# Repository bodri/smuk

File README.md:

# 🚀 smuk
An SMU by kapuki

This repository is structured as a unified monorepo containing both the physical hardware designs (schematics, PCB, enclosures) and the bare-metal C firmware.

---

## 📂 Project Architecture

The workspace is split into isolated modules to decouple hardware revisions from compilation build systems:

```text
smuk/
├── firmware/       # Core firmware application, drivers, and build targets
├── hardware/       # Electrical schematics, PCB layout, and production packages
├── AGENTS.md       # Target rules and context for AI assistants (Claude, Codex)
└── README.md       # This file
```

---

## 📐 1. Hardware Module (`/hardware`)

The electronics are designed using **KiCad 10.0** (or your preferred EDA tool), leveraging the high-performance capabilities of the **STM32H5** series (Cortex-M33 with TrustZone support).

### Key Subdirectories
* **`/pcb`**: Contains the source `.kicad_pro`, `.kicad_sch`, and `.kicad_pcb` files.
* **`/mechanical`**: STEP files for the enclosure, 3D component models, and mounting layouts.
* **`/production`**: **Production-ready files.** Check this folder if you need to quickly inspect the schematics without installing the full EDA design suite.

### Quick Hardware Access
* 📄 **Latest Schematic PDF**: [`/hardware/production/schematic.pdf`](hardware/production/) *(Update path to exact filename)*
* 📦 **Gerber Packages / BOM**: Prepared inside [`/hardware/production/`](hardware/production/) for direct manufacturing ordering.

---

## 💻 2. Firmware Module (`/firmware`)

The software environment is built on top of the **STM32 Cube Hardware Abstraction Layer (HAL)** and configured for cross-compilation using the **GNU ARM Embedded Toolchain**.

### Current Firmware Status

Firmware targets the **STM32H503RB**. ADS131M03 SPI/DMA acquisition, physical measurement conversion, CALBUS and voltage calibration, and persistent Flash calibration storage are working.

Range control, PA safety, watchdog, and parts of the platform interface still contain placeholders awaiting hardware integration. The `App` directory is unfinished and is excluded from the firmware source list.

### Core Architecture

```text
firmware/
├── Core/                 # CubeMX initialization, callbacks, integration loop
├── Drivers/SMU/          # ADC, measurement, calibration and hardware interfaces
├── Platform/STM32H503/   # Board-specific HAL implementations
├── Storage/             # Persistent calibration records and Flash storage
├── App/                 # Unfinished instrument/control implementation
├── tests/               # Host regression tests
└── smuk.ioc              # STM32CubeMX configuration
```

`Drivers` also contains the vendor CMSIS, STM32H5 HAL, and board support libraries. `Drivers/SMU/ads131m03.h/.c` contains both blocking device bring-up and DMA acquisition. Its HAL operations are provided through `ads131m03_port.h`, implemented in `Platform/STM32H503/ads131m03_port_hal.c`.

`smu_measurement` converts raw ADC samples into physical measurements and applies calibration and filtering. `smu_calibration` manages active coefficients, `smu_cal_seq` sequences calibration acquisition, and `Storage/calibration_store` persists calibration records.

> ⚠️ **Crucial Development Rule:** In CubeMX-generated files, write custom C code only inside the explicit `/* USER CODE BEGIN ... */` and `/* USER CODE END ... */` sections. Changes outside these sections may be lost when `smuk.ioc` is regenerated. This restriction does not apply to handwritten drivers and modules.

### Calibration Behavior

Calibration discard and acquisition phases each have a configurable timeout, defaulting to **1,000 ms** per phase. The sequencer accounts for elapsed scheduler time, including delayed ticks. On timeout, it opens calibration relays, selects zero CALBUS, requests PA disable and ranges off through the existing hardware interfaces, and latches a fault until sequencer reinitialization. PA and range actions still depend on the placeholder implementations described above.

Applying calibration coefficients preserves measurement ranges, validity/compliance/transition flags, sample count, and filter configuration. Filter history resets to avoid blending values from different calibrations, and cached outputs remain invalid until another frame is processed. Startup still performs full measurement initialization.

### Calibration Flash Reservation

Application Flash is limited to **112 KiB**, enforced by `check_limits.py` during the build. Two **8 KiB** calibration slots occupy the remaining 16 KiB:

| Region | Address range |
| --- | --- |
| Application | `0x08000000`–`0x0801BFFF` |
| Calibration A | `0x0801C000`–`0x0801DFFF` |
| Calibration B | `0x0801E000`–`0x0801FFFF` |

Saves replace the older or invalid slot and verify the replacement by record validation and byte-for-byte readback. The newest valid calibration is preserved while the replacement is written. Storage initialization does not erase calibration; loading falls back to default coefficients if neither slot is valid.

---

## 🛠️ Getting Started (Compilation & Flashing)

For project guidance, see [AGENTS.md](./AGENTS.md) and the firmware-specific [firmware/AGENTS.md](./firmware/AGENTS.md).

### Prerequisites

Install these dependencies and make them available on `PATH`:

1. **ARM GCC toolchain and binutils** (`arm-none-eabi-gcc`, `arm-none-eabi-size`, `arm-none-eabi-objcopy`)
2. **CMake 3.22+** and **Ninja**
3. **Python 3** for the Flash footprint check
4. A **host C compiler** (`cc`, or set `CC`) for host regression tests

`clang-format` and `cppcheck` are optional. When installed, the build script automatically formats C source and header files under `Core/Src`, `Core/Inc`, `Platform`, `Drivers/SMU`, and `Storage`, and runs static analysis on `Core`, `Platform`, `Drivers/SMU`, and `Storage`. These steps are skipped with a warning if the tools are unavailable.

The supplied flashing and debugging helpers currently require **STM32CubeIDE installed under `/Applications` on macOS**, including its STM32CubeProgrammer and ST-LINK GDB server bundles.

### Build and Test

From the repository root:

```bash
cd firmware
./build.sh
sh tests/run_calibration_state.sh
```

The build uses the ARM toolchain through CMake and Ninja, generates `build/smuk.elf`, `build/smuk.hex`, and `build/smuk.bin`, and checks the 112 KiB application Flash limit.

The host regression tests cover calibration timeouts and cleanup, successful acquisition, zero-CALBUS offset capture, and measurement state preservation when applying coefficients. They run without a connected board and do not replace hardware verification.

In Zed, use **STM32H5: Build Firmware** or the configured build shortcut (`cmd-b` / `ctrl-b`). The **STM32H5: Clean & Rebuild Firmware** task currently passes `--clean`, but `build.sh` does not implement special handling for that argument. Each normal build clears the CMake cache and configuration directory; for a complete clean build, remove `firmware/build` before running the script.

### Hardware Flashing

Connect the board through an ST-LINK debugger, build the firmware, then run from `firmware`:

```bash
./flash.sh
```

The helper programs `build/smuk.elf` using STM32CubeProgrammer over SWD in under-reset mode, verifies the image, and resets the target. The equivalent Zed task is **STM32H5: Flash Firmware**.

### Serial Communication and Manual Calibration

The ST-LINK USB connection provides a USART3 Virtual COM Port at **115200 baud,
8N1, no flow control**. The firmware console supports measurement/raw queries,
range selection, and manual calibration from externally applied references.
Start with `HELP` or `PING`. Select precision windows with `INTEGRATION
1MS|8MS|20MS|50MS|100MS`; precision readings become valid after the window fills.
`CAL:SHOW?` reports calibration provenance, and captures report noise/drift. `ACQ?` reports acquisition health; measurement
queries report freshness, settling, precision readiness, and channel clipping.
Stale acquisition invalidates readings, and persistent failures latch an ADC fault. Current and voltage autorange are controlled
independently with `AUTORANGE:I` and `AUTORANGE:V`; current autorange defaults ON and voltage autorange defaults OFF.
Input loading defaults to HIGHZ, keeping MV_ON LOW; use `IMPEDANCE 10M`
to connect the 10 MΩ resistor.
Voltage starts fixed at 15 V, keeping VRANGE LOW. When explicitly enabled, voltage autorange switches up at 6.2 V magnitude and down at
5.0 V after 100 ms. Disable both autoranges during manual calibration.

See [Serial console and manual calibration](firmware/serial_console.md) for the
command list, terminal setup, calibration capture/fit/save workflow, and host tests.

### Debug Server

From `firmware`, run:

```bash
./debug_server.sh
```

This starts the ST-LINK GDB server on port **61234**. Connect a GDB client configured for the ARM target and `build/smuk.elf`. The equivalent Zed task is **STM32H5: Start GDB Debug Server**.

---

## 🏷️ Versioning Strategy

This project adheres to **Semantic Versioning (v2.0.0)**. Due to the monorepo nature, git tags tie firmware releases directly to specific physical board iterations:
* **`v1.0.0-HW1`**: Initial hardware board spin layout.
* **`v1.0.1-FW`**: Firmware patch fixing a register timing error specifically for the HW1 board revision.

The measurement firmware now uses a nominal 2-second independent watchdog.
Foreground processing owns refresh; handled faults stay latched for diagnosis.
See the [watchdog and CubeMX setup instructions](firmware/serial_console.md#independent-watchdog)
for regeneration settings, reset reporting, and bench checks.

## Desktop measurement console

The [desktop application](desktop/README.md) provides live measurements, observed
statistics, range/autorange controls, integration and impedance selection, and
serial diagnostics on macOS. It uses the existing console protocol; firmware
and hardware remain separate projects.

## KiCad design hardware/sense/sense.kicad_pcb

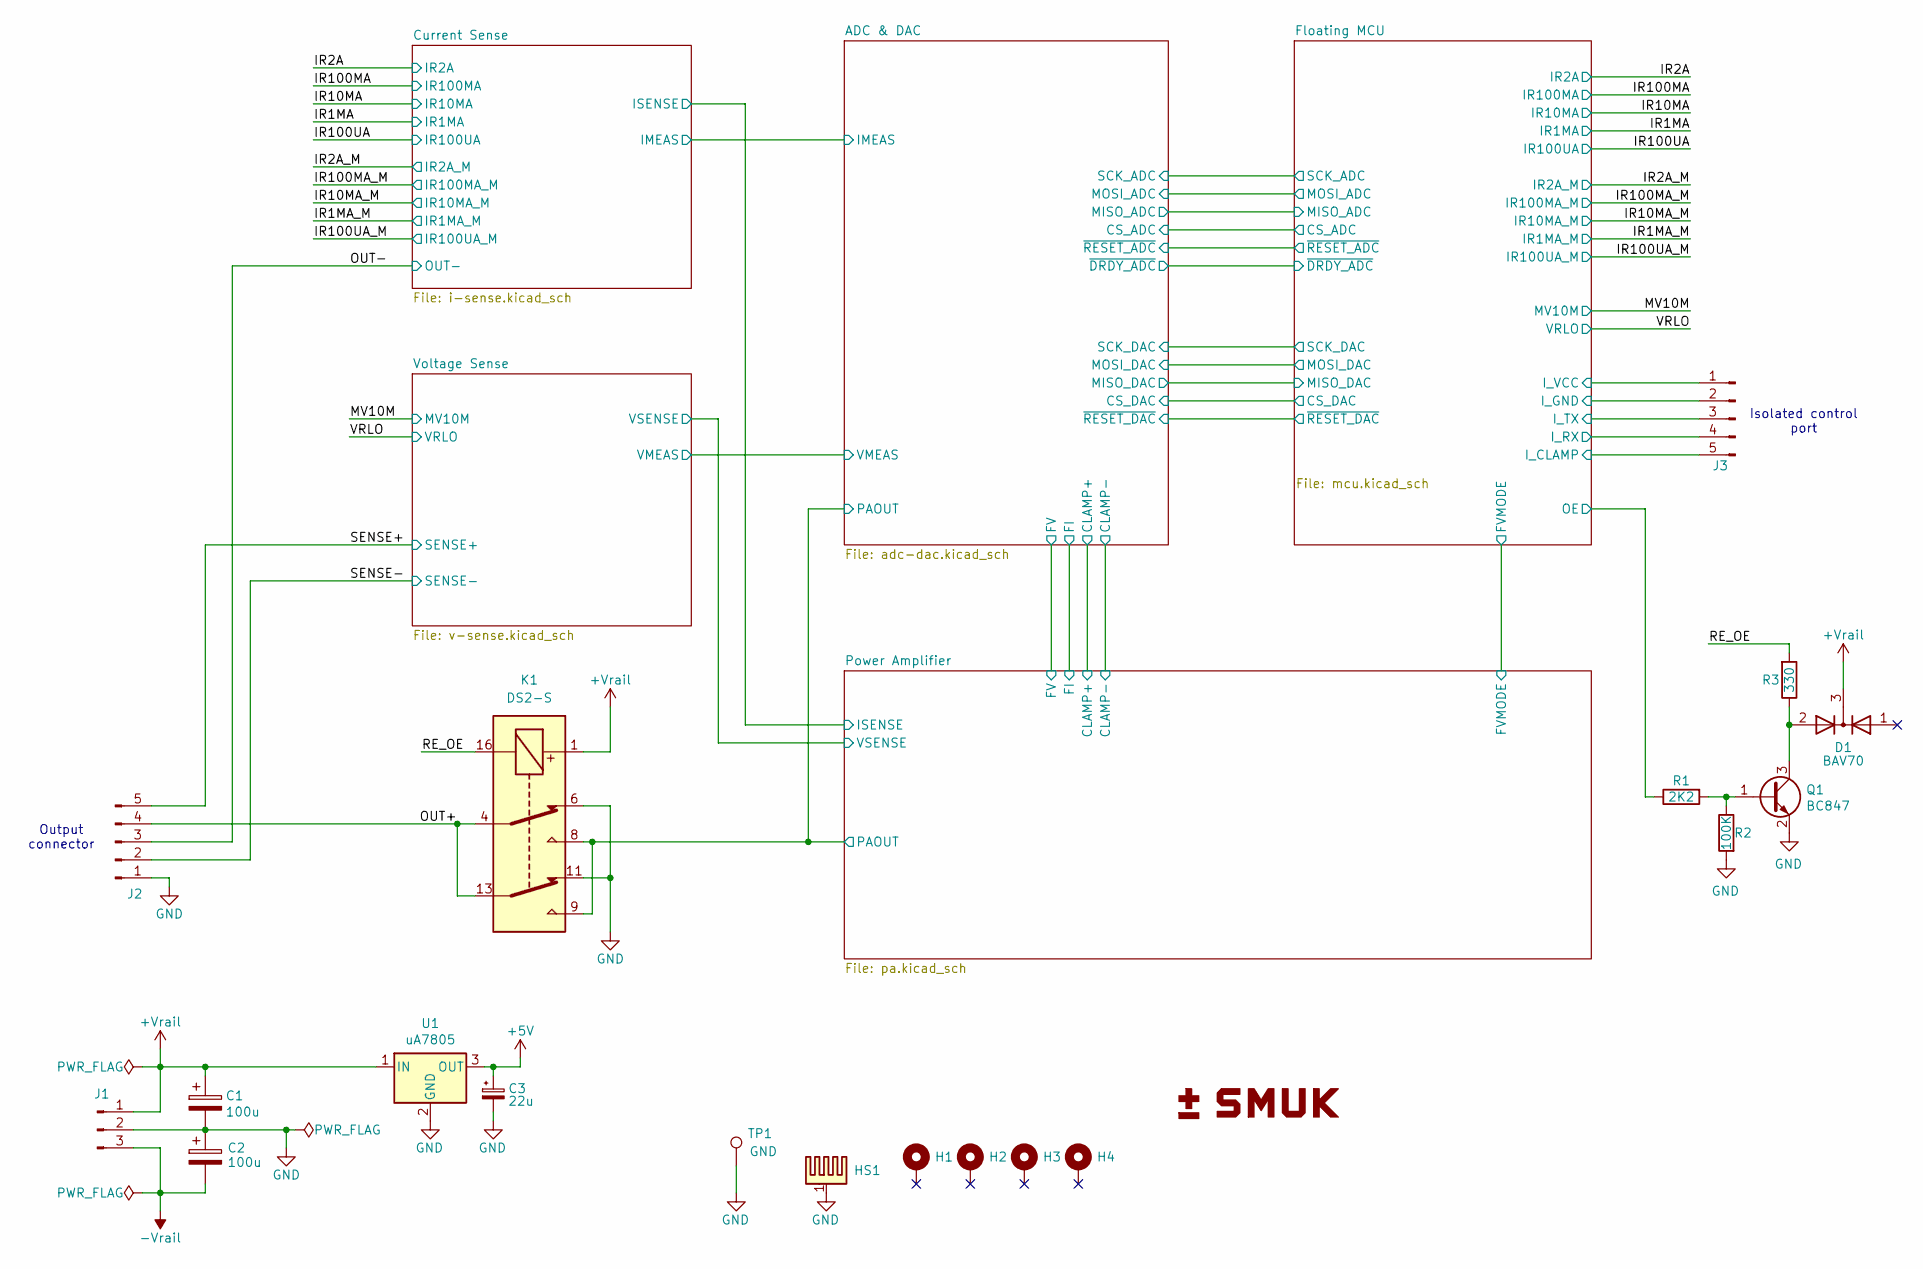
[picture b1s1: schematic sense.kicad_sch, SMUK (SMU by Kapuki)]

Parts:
C1, C2: 100u; C_Elec_10x10.2
C3: 22u; CP_EIA-6032-28_Kemet-C
D1: BAV70; SOT-23
H1, H2, H3, H4: MountingHole_Pad_MP; MountingHole_3.2mm_M3_Pad_Via
HS1: Heatsink_Pad; Heatsink_Fischer_SK96-84SA_2Fixations
J1: Conn_01x03_Pin; Molex_KK-396_A-41791-0003_1x03_P3.96mm_Vertical
J2: Conn_01x05_Male; Molex_KK-396_A-41791-0005_1x05_P3.96mm_Vertical
J3: Conn_01x05_Pin; Molex_KK-254_AE-6410-05A_1x05_P2.54mm_Vertical
K1: DS2-S; Relay_DPDT_Panasonic_DS2_S
Q1: BC847; SOT-23
R1: 2K2; R_0603_1608Metric
R2: 100K; R_0603_1608Metric
R3: 330; R_1206_3216Metric
TP1: GND; TestPoint_Loop_D1.80mm_Drill1.0mm_Beaded
U1: uA7805; TO-263-3_TabPin2

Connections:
+5V: C3.1, U1.3 (OUT); also elsewhere on the board
+Vrail: C1.1, D1.3 (K), J1.1, K1.1, U1.1 (IN); also elsewhere on the board
-Vrail: C2.2, J1.3; also elsewhere on the board
/ADC & DAC/PAOUT: K1.8, K1.9; also elsewhere on the board
/Floating MCU/I_CLAMP: J3.5; also elsewhere on the board
/Floating MCU/I_GND: J3.2; also elsewhere on the board
/Floating MCU/I_RX: J3.4; also elsewhere on the board
/Floating MCU/I_TX: J3.3; also elsewhere on the board
/Floating MCU/I_VCC: J3.1; also elsewhere on the board
/Floating MCU/OE: R1.1; also elsewhere on the board
/OUT+: J2.4, K1.4, K1.13
/OUT-: J2.3; also elsewhere on the board
/RE_OE: K1.16, R3.2
/SENSE+: J2.5; also elsewhere on the board
/SENSE-: J2.2; also elsewhere on the board
GND: C1.2, C2.1, C3.2, HS1.1, J1.2, J2.1, K1.6, K1.11, Q1.2 (E), R2.2, TP1.1 (1_1), U1.2 (GND); also elsewhere on the board
unnamed: Q1.1 (B), R1.2, R2.1
unnamed: D1.2 (A), Q1.3 (C), R3.1

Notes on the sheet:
Isolated control port
Output connector

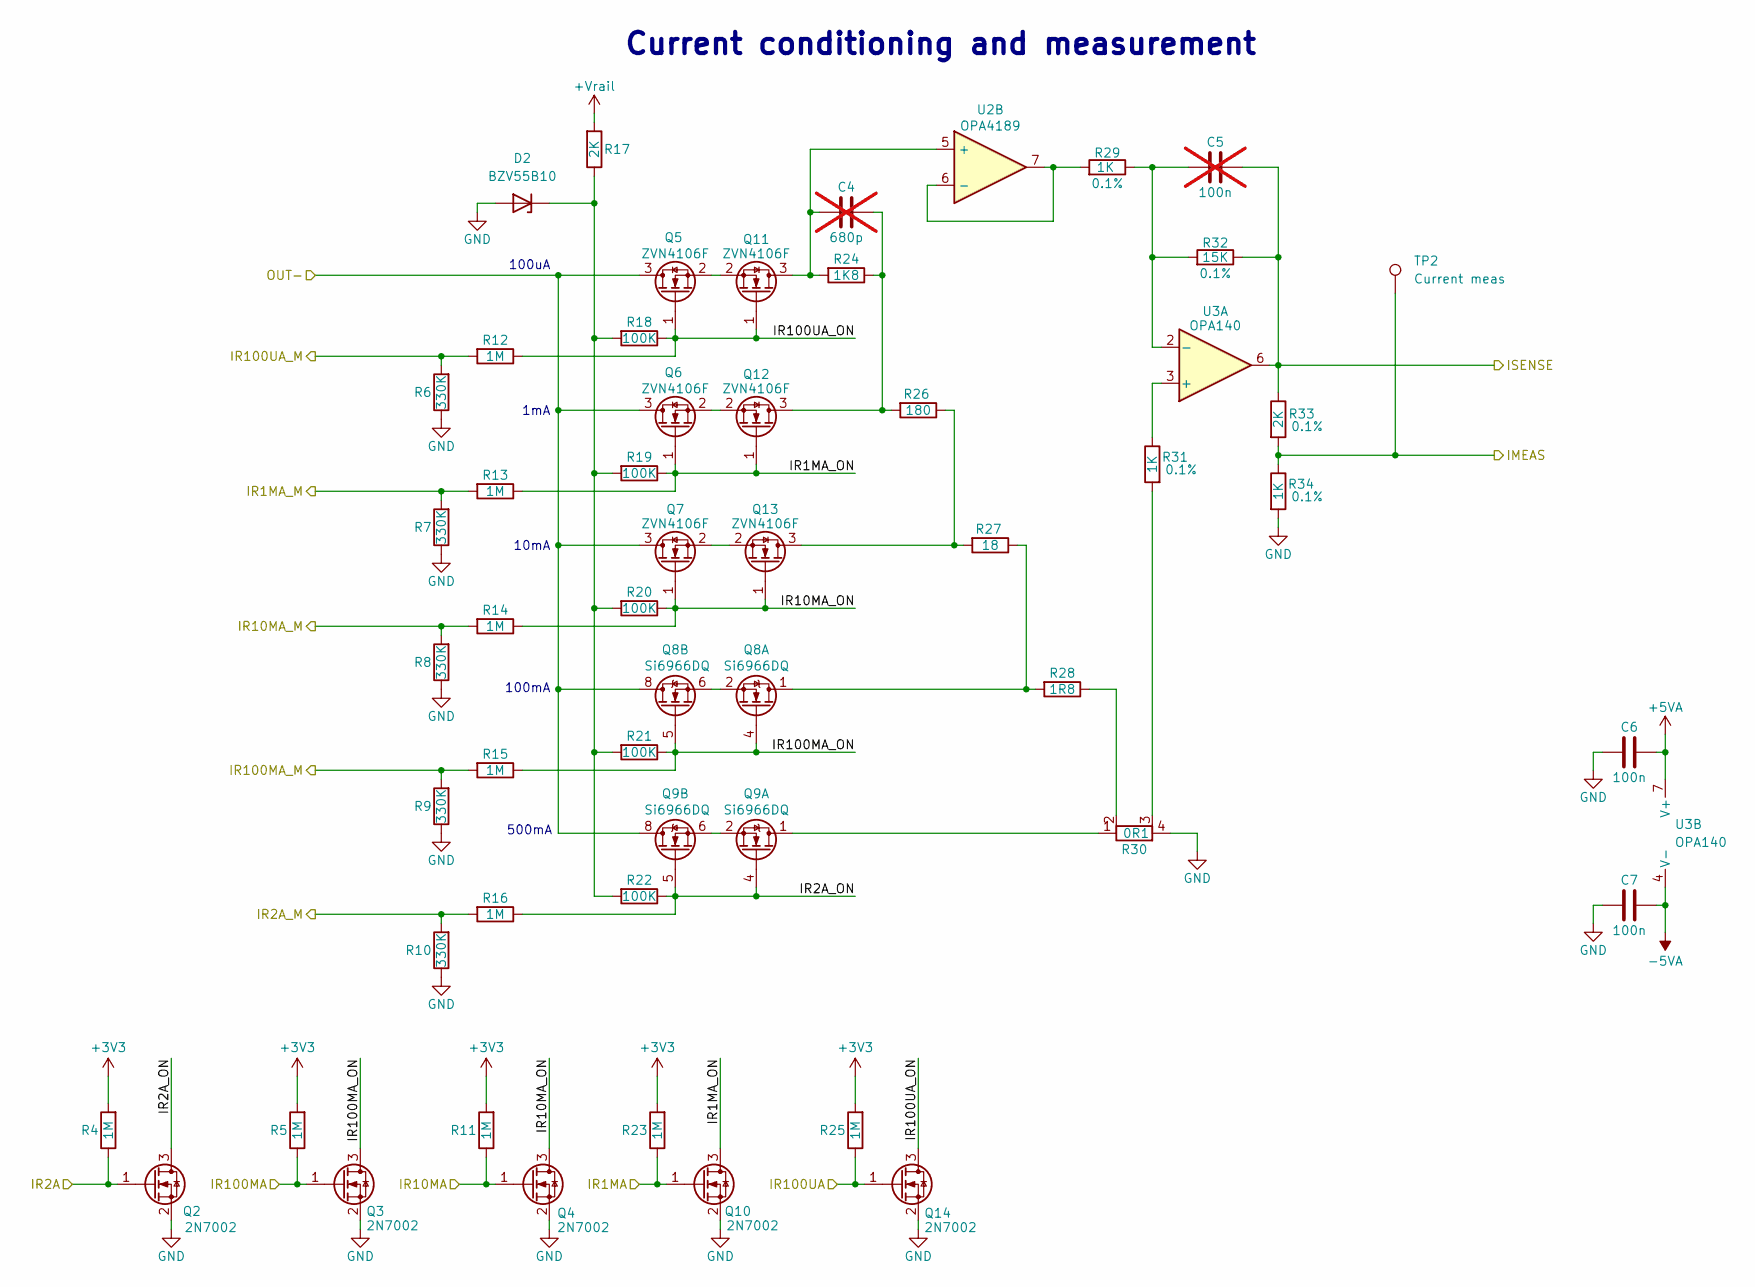
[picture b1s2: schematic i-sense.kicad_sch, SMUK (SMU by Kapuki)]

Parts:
C4: 680p; C_0603_1608Metric; not fitted
C5: 100n; C_0603_1608Metric; not fitted
C6, C7: 100n; C_0603_1608Metric
D2: BZV55B10; D_MiniMELF
Q2, Q3, Q4, Q10, Q14: 2N7002; SOT-23
Q5, Q6, Q7, Q11, Q12, Q13: ZVN4106F; SOT-23
Q8, Q9: Si6966DQ; TSSOP-8_4.4x3mm_P0.65mm
R4, R5, R11, R12, R13, R14, R15, R16, R23, R25: 1M; R_0603_1608Metric
R6, R7, R8, R9, R10: 330K; R_0603_1608Metric
R17, R33: 2K; R_0603_1608Metric
R18, R19, R20, R21, R22: 100K; R_0603_1608Metric
R24: 1K8; R_1206_3216Metric
R26: 180; R_1206_3216Metric
R27: 18; R_1206_3216Metric
R28: 1R8; R_1206_3216Metric
R29, R31, R34: 1K; R_0603_1608Metric
R30: 0R1; Littelfuse L4CL1206
R32: 15K; R_0603_1608Metric
TP2: Current meas; TestPoint_Pad_D1.5mm
U2: OPA4189; TSSOP-14_4.4x5mm_P0.65mm
U3: OPA140; SOIC-8_3.9x4.9mm_P1.27mm

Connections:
+3V3: R4.2, R5.2, R11.2, R23.2, R25.2; also elsewhere on the board
+5VA: C6.1, U3.7 (V+); also elsewhere on the board
+Vrail: R17.2; also elsewhere on the board
-5VA: C7.1, U3.4 (V-); also elsewhere on the board
/ADC & DAC/IMEAS: R33.2, R34.1, TP2.1 (1_1); also elsewhere on the board
/Current Sense/IR1MA_ON: Q6.1 (G), Q10.3 (D), Q12.1 (G), R13.1, R19.1
/Current Sense/IR2A_ON: Q2.3 (D), Q9.4 (G1), Q9.5 (G2), R16.1, R22.1
/Current Sense/IR10MA_ON: Q4.3 (D), Q7.1 (G), Q13.1 (G), R14.1, R20.1
/Current Sense/IR100MA_ON: Q3.3 (D), Q8.4 (G1), Q8.5 (G2), R15.1, R21.1
/Current Sense/IR100UA_ON: Q5.1 (G), Q11.1 (G), Q14.3 (D), R12.1, R18.1
/Current Sense/ISENSE: C5.1, R32.1, R33.1, U3.6; also elsewhere on the board
/IR1MA: Q10.1 (G), R23.1; also elsewhere on the board
/IR1MA_M: R7.2, R13.2; also elsewhere on the board
/IR2A: Q2.1 (G), R4.1; also elsewhere on the board
/IR2A_M: R10.2, R16.2; also elsewhere on the board
/IR10MA: Q4.1 (G), R11.1; also elsewhere on the board
/IR10MA_M: R8.2, R14.2; also elsewhere on the board
/IR100MA: Q3.1 (G), R5.1; also elsewhere on the board
/IR100MA_M: R9.2, R15.2; also elsewhere on the board
/IR100UA: Q14.1 (G), R25.1; also elsewhere on the board
/IR100UA_M: R6.2, R12.2; also elsewhere on the board
/OUT-: Q5.3 (D), Q6.3 (D), Q7.3 (D), Q8.8 (D2), Q9.8 (D2); also elsewhere on the board
GND: C6.2, C7.2, D2.2 (A), Q2.2 (S), Q3.2 (S), Q4.2 (S), Q10.2 (S), Q14.2 (S), R6.1, R7.1, R8.1, R9.1, R10.1, R30.4, R34.2; also elsewhere on the board
unnamed: D2.1 (K), R17.1, R18.2, R19.2, R20.2, R21.2, R22.2
unnamed: Q8.1 (D1), R27.1, R28.2
unnamed: Q8.2 (S1), Q8.3 (S1), Q8.6 (S2), Q8.7 (S2)
unnamed: Q9.1 (D1), R30.1
unnamed: Q9.2 (S1), Q9.3 (S1), Q9.6 (S2), Q9.7 (S2)
unnamed: C4.2, Q11.3 (D), R24.2, U2.5 (+)
unnamed: Q5.2 (S), Q11.2 (S)
unnamed: C4.1, Q12.3 (D), R24.1, R26.2
unnamed: Q6.2 (S), Q12.2 (S)
unnamed: Q13.3 (D), R26.1, R27.2
unnamed: Q7.2 (S), Q13.2 (S)
unnamed: R28.1, R30.2
unnamed: R30.3, R31.2
unnamed: R29.2, U2.6 (-), U2.7
unnamed: R31.1, U3.3 (+)
unnamed: C5.2, R29.1, R32.2, U3.2 (-)

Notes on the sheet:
100mA
100uA
1mA
500mA
10mA
Current conditioning and measurement

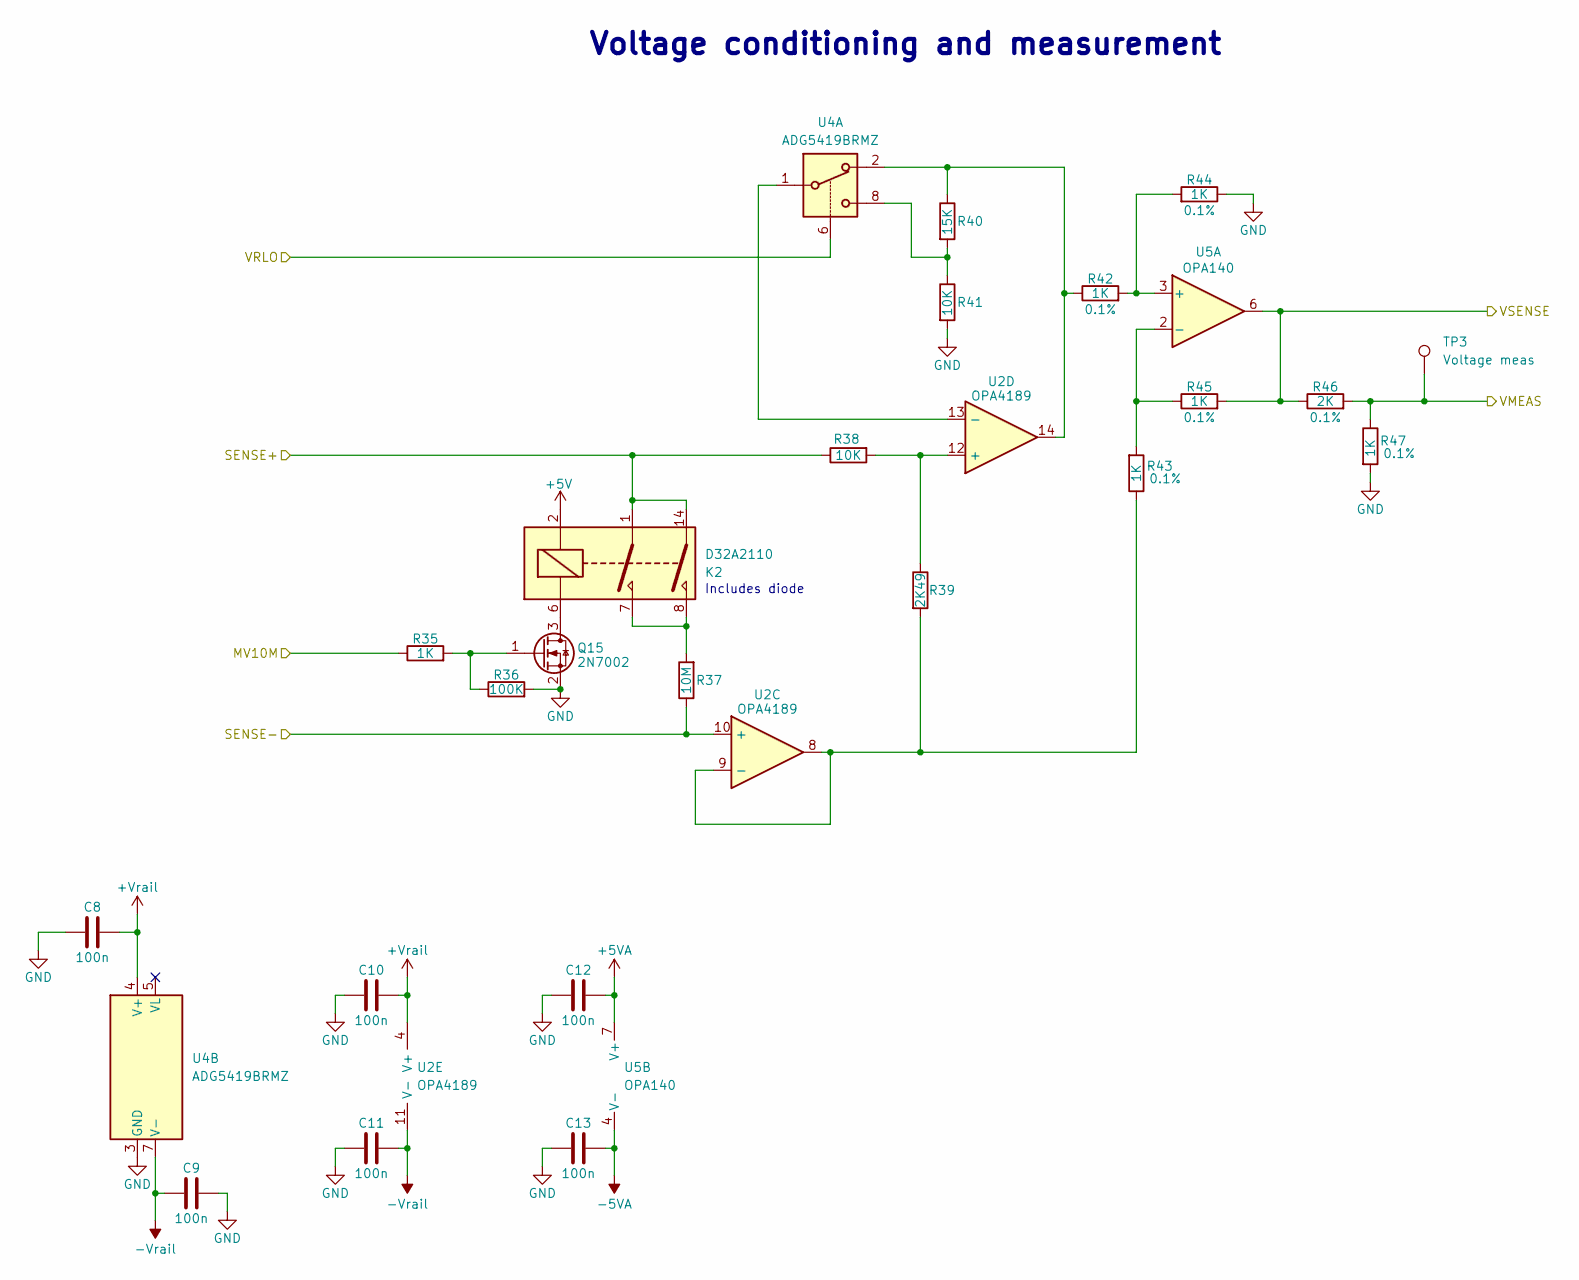
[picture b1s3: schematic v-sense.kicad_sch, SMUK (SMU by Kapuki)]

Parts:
C8, C9, C10, C11, C12, C13: 100n; C_0603_1608Metric
K2: D32A2110; Relay_StandexMeder_DIP_LowProfile
Q15: 2N7002; SOT-23
R35, R42, R43, R44, R45, R47: 1K; R_0603_1608Metric
R36: 100K; R_0603_1608Metric
R37: 10M; R_1206_3216Metric
R38, R41: 10K; R_0603_1608Metric
R39: 2K49; R_0603_1608Metric
R40: 15K; R_0603_1608Metric
R46: 2K; R_0603_1608Metric
TP3: Voltage meas; TestPoint_Pad_D1.5mm
U2: OPA4189; TSSOP-14_4.4x5mm_P0.65mm
U4: ADG5419BRMZ; MSOP-8_3x3mm_P0.65mm
U5: OPA140; SOIC-8_3.9x4.9mm_P1.27mm

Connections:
+5V: K2.2; also elsewhere on the board
+5VA: C12.1, U5.7 (V+); also elsewhere on the board
+Vrail: C8.1, C10.1, U2.4 (V+), U4.4 (V+); also elsewhere on the board
-5VA: C13.1, U5.4 (V-); also elsewhere on the board
-Vrail: C9.1, C11.1, U2.11 (V-), U4.7 (V-); also elsewhere on the board
/ADC & DAC/VMEAS: R46.2, R47.1, TP3.1 (1_1); also elsewhere on the board
/MV10M: R35.1; also elsewhere on the board
/Power Amplifier/VSENSE: R45.2, R46.1, U5.6; also elsewhere on the board
/SENSE+: K2.1, K2.14, R38.1; also elsewhere on the board
/SENSE-: R37.1, U2.10 (+); also elsewhere on the board
/VRLO: U4.6; also elsewhere on the board
GND: C8.2, C9.2, C10.2, C11.2, C12.2, C13.2, Q15.2 (S), R36.2, R41.2, R44.1, R47.2, U4.3 (GND); also elsewhere on the board
unnamed: K2.7, K2.8, R37.2
unnamed: K2.6, Q15.3 (D)
unnamed: Q15.1 (G), R35.2, R36.1
unnamed: R40.1, R42.1, U2.14, U4.2
unnamed: R40.2, R41.1, U4.8
unnamed: R39.2, R43.1, U2.8, U2.9 (-)
unnamed: R38.2, R39.1, U2.12 (+)
unnamed: U2.13 (-), U4.1
unnamed: R42.2, R44.2, U5.3 (+)
unnamed: R43.2, R45.1, U5.2 (-)

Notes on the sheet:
Voltage conditioning and measurement
Includes diode

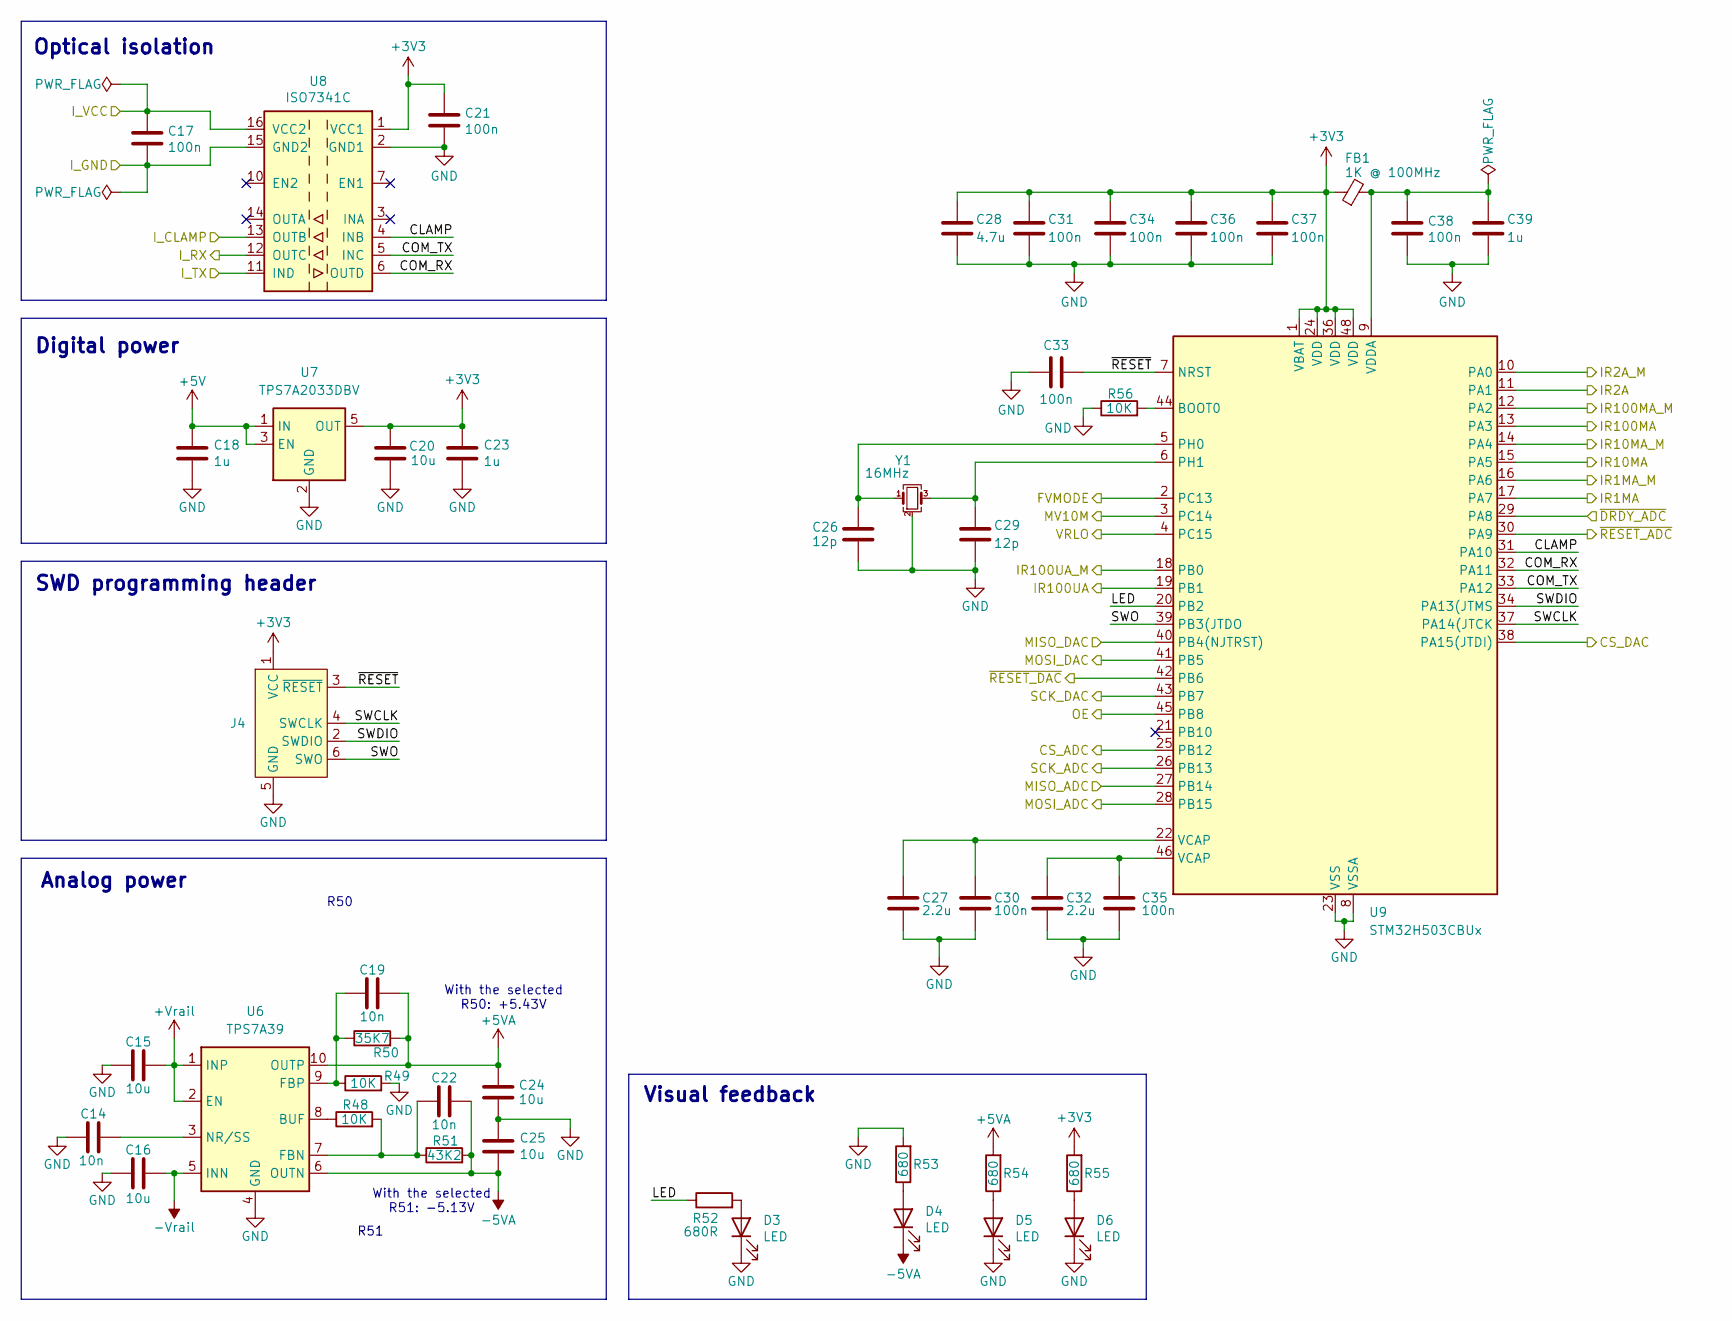
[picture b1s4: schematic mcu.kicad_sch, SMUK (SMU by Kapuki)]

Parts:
C14, C19, C22: 10n; C_0603_1608Metric
C15, C16: 10u; C_1210_3225Metric
C17, C21, C30, C31, C33, C34, C35, C36, C37, C38: 100n; C_0603_1608Metric
C18, C23, C39: 1u; C_0603_1608Metric
C20: 10u; C_1206_3216Metric
C24, C25: 10u; C_0805_2012Metric
C26, C29: 12p; C_0603_1608Metric
C27, C32: 2.2u; C_0603_1608Metric
C28: 4.7u; C_0603_1608Metric
D3, D4, D5, D6: LED; LED_0603_1608Metric
FB1: 1K @ 100MHz; L_0603_1608Metric
J4: Tag Connector; Tag-Connect_TC2030-IDC-NL_2x03_P1.27mm_Vertical
R48, R49, R56: 10K; R_0603_1608Metric
R50: 35K7; R_0603_1608Metric
R51: 43K2; R_0603_1608Metric
R52: 680R; R_0603_1608Metric
R53, R54, R55: 680; R_0603_1608Metric
U6: TPS7A39; Texas_S-PVSON-N10_ThermalVias
U7: TPS7A2033DBV; SOT-23-5
U8: ISO7341C; SOIC-16W_7.5x10.3mm_P1.27mm
U9: STM32H503CBUx; QFN-48-1EP_7x7mm_P0.5mm_EP5.6x5.6mm
Y1: 16MHz; Crystal_SMD_SeikoEpson_FA238-4Pin_3.2x2.5mm

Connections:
+3V3: C20.1, C21.1, C23.1, C28.1, C31.1, C34.1, C36.1, C37.1, FB1.1, J4.1 (VCC), R55.2, U7.5 (OUT), U8.1 (VCC1), U9.1 (VBAT), U9.24 (VDD), U9.36 (VDD), U9.48 (VDD); also elsewhere on the board
+5V: C18.1, U7.1 (IN), U7.3 (EN); also elsewhere on the board
+5VA: C19.1, C24.1, R50.2, R54.2, U6.10 (OUTP); also elsewhere on the board
+Vrail: C15.1, U6.1 (INP), U6.2 (EN); also elsewhere on the board
-5VA: C22.1, C25.2, D4.1 (K), R51.2, U6.6 (OUTN); also elsewhere on the board
-Vrail: C16.1, U6.5 (INN); also elsewhere on the board
/ADC & DAC/CS_ADC: U9.25 (PB12); also elsewhere on the board
/ADC & DAC/CS_DAC: U9.38 (PA15(JTDI)); also elsewhere on the board
/ADC & DAC/MISO_ADC: U9.27 (PB14); also elsewhere on the board
/ADC & DAC/MISO_DAC: U9.40 (PB4(NJTRST)); also elsewhere on the board
/ADC & DAC/MOSI_ADC: U9.28 (PB15); also elsewhere on the board
/ADC & DAC/MOSI_DAC: U9.41 (PB5); also elsewhere on the board
/ADC & DAC/SCK_ADC: U9.26 (PB13); also elsewhere on the board
/ADC & DAC/SCK_DAC: U9.43 (PB7); also elsewhere on the board
/ADC & DAC/~DRDY_ADC: U9.29 (PA8); also elsewhere on the board
/ADC & DAC/~RESET_ADC: U9.30 (PA9); also elsewhere on the board
/ADC & DAC/~RESET_DAC: U9.42 (PB6); also elsewhere on the board
/Floating MCU/CLAMP: U8.4 (INB), U9.31 (PA10)
/Floating MCU/COM_RX: U8.6 (OUTD), U9.32 (PA11)
/Floating MCU/COM_TX: U8.5 (INC), U9.33 (PA12)
/Floating MCU/FVMODE: U9.2 (PC13); also elsewhere on the board
/Floating MCU/I_CLAMP: U8.13 (OUTB); also elsewhere on the board
/Floating MCU/I_GND: C17.2, U8.9 (GND2), U8.15 (GND2); also elsewhere on the board
/Floating MCU/I_RX: U8.12 (OUTC); also elsewhere on the board
/Floating MCU/I_TX: U8.11 (IND); also elsewhere on the board
/Floating MCU/I_VCC: C17.1, U8.16 (VCC2); also elsewhere on the board
/Floating MCU/LED: R52.1, U9.20 (PB2)
/Floating MCU/OE: U9.45 (PB8); also elsewhere on the board
/Floating MCU/SWCLK: J4.4 (SWCLK), U9.37 (PA14(JTCK)
/Floating MCU/SWDIO: J4.2 (SWDIO), U9.34 (PA13(JTMS)
/Floating MCU/SWO: J4.6 (SWO), U9.39 (PB3(JTDO)
/Floating MCU/~RESET: C33.2, J4.3 (~RESET), U9.7 (NRST)
/IR1MA: U9.17 (PA7); also elsewhere on the board
/IR1MA_M: U9.16 (PA6); also elsewhere on the board
/IR2A: U9.11 (PA1); also elsewhere on the board
/IR2A_M: U9.10 (PA0); also elsewhere on the board
/IR10MA: U9.15 (PA5); also elsewhere on the board
/IR10MA_M: U9.14 (PA4); also elsewhere on the board
/IR100MA: U9.13 (PA3); also elsewhere on the board
/IR100MA_M: U9.12 (PA2); also elsewhere on the board
/IR100UA: U9.19 (PB1); also elsewhere on the board
/IR100UA_M: U9.18 (PB0); also elsewhere on the board
/MV10M: U9.3 (PC14); also elsewhere on the board
/VRLO: U9.4 (PC15); also elsewhere on the board
GND: C14.2, C15.2, C16.2, C18.2, C20.2, C21.2, C23.2, C24.2, C25.1, C26.2, C27.2, C28.2, C29.2, C30.2, C31.2, C32.2, C33.1, C34.2, C35.2, C36.2, C37.2, C38.2, C39.2, D3.1 (K), D5.1 (K), D6.1 (K), J4.5 (GND), R49.2, R53.2, R56.1, U6.4 (GND), U6.11 (GND), U7.2 (GND), U8.2 (GND1), U8.8 (GND1), U9.8 (VSSA), U9.23 (VSS), U9.35 (VSS), U9.47 (VSS), U9.49 (VSS), Y1.2 (G), Y1.4 (G); also elsewhere on the board
unnamed: C27.1, C30.1, U9.22 (VCAP)
unnamed: C32.1, C35.1, U9.46 (VCAP)
unnamed: D3.2 (A), R52.2
unnamed: D4.2 (A), R53.1
unnamed: D5.2 (A), R54.1
unnamed: D6.2 (A), R55.1
unnamed: R48.1, U6.8 (BUF)
unnamed: C22.2, R48.2, R51.1, U6.7 (FBN)
unnamed: C19.2, R49.1, R50.1, U6.9 (FBP)
unnamed: C14.1, U6.3 (NR/SS)
unnamed: R56.2, U9.44 (BOOT0)
unnamed: C26.1, U9.5 (PH0), Y1.1
unnamed: C29.1, U9.6 (PH1), Y1.3
unnamed: C38.1, C39.1, FB1.2, U9.9 (VDDA)

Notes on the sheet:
Digital power
SWD programming header
Analog power
With the selected R50: +5.43V
Optical isolation
With the selected R51: -5.13V
R51
Visual feedback
R50
